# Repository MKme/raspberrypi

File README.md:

# raspi

<p align="center">
<b>Erics Raspberry Pi Randomness</b><br>
Open Source<br><br>
<br>🐦 <a href="https://twitter.com/mkmeorg">Twitter</a>
| 📺 <a href="https://www.youtube.com/mkmeorg">YouTube</a>
| 🌍 <a href="http://www.mkme.org">mkme.org</a><br>
<br>
Support this project and become a patron on <a href="https://www.patreon.com/EricWilliam">Patreon</a>.<br>
Chat: <a href="https://discord.gg/j9S4Fgv">Discord</a></b>!
</p>

# Raspberry Pi Stuffz
My Boards, programming and ref materials and all my random notes and files to make life easier

# Handy Linux Commands
sudo reboot

man : gives manual on any command

clear

cntrl-L Does the same as clear

whoami

pwd    - print working diectory

cd ~   - back to home dir

cd /

top     - Shows a list of processes running q- to quit

rm     - remove file/direct

ls -l   :show details

ls -a   : all files including hidden

ls -p  :puts a / after directories

ls -la   : both details and all files

ls -lap   : USE THIS 

df -h    : Show disk space!

sudo- gives root permissions

mv -move

mkdir

sudo -i Become Root

exit or ctrl-D to exit Root superuser

help popd | more  -if a command doesnt have a manual try help 

ifconfig -Show network connections

ip address - IP info

ip maddress - MAC adress

whoami -Tells you username

$(whoami) runs command and uses the result for piping

ps aux | grep -v $(whoami) - Returns all process running Not by current user (-v means NOT equal in Linux)

file test.py -File gives the info on what a file is and whats inside- 

less test.py -Command line text editor- Q to quit

acl -calendar

cat > test.txt  -Will pipe your typed output to file, Ctrl-D to exit

Bash- learn more on this- should be on all systems

Running Scripts:

sh test.py will run test in shell

Type chmod a+x hello.py to make executable

Type ./hello.py to run your program!

GetLinux Releaxse Info:

more /etc/*release   

or

cat /etc/*release

free -h  -Free memory stats in human readable with -h

df -h -Gives free disk space

locate xxx  -Will search the file index and return results found

find /etc/ -name *.conf    -Will return all conf files in that directory & subdirectories

Cool Screensaver in terminal!

cmatrix -s -Once installed via apt-get install -s will exit from any key.  AWESOME screensaver -bs for bold

### Handy  

Awesome tutorial dual boot etc and Kodi
https://www.youtube.com/watch?v=hLs5V-GNJjg

Scratch with Kinect-Awesome
https://www.youtube.com/watch?v=LpPDnRVIYcM

Screencapture/VNC connection to Pi!
https://www.youtube.com/watch?v=EfAmq8TgHes

Basic setup to achieve above VNC:
https://www.youtube.com/watch?v=c5QCoh8S0N4

VNC into Pi- Some great tips on finding it!  End is complex with ssh etc
https://www.youtube.com/watch?v=S6tnNBlqtNI

##VNC 

Install vnc:

sudo apt-get install tightvncserver

tightvncserver

Add password:raspberr

vncserver :1 -geometry 800x600 -depth 24

or

vncserver :1 -geometry 1280x720 -depth 24

##HANDY 

E- WORKS but need to login via ssh Start VNC on Startup:  https://www.youtube.com/watch?v=JXnnhTvvVZk

ADA version no worky  https://learn.adafruit.com/adafruit-raspberry-pi-lesson-7-remote-control-with-vnc/running-vncserver-at-startup

*****E note- do ADA method via vnc file access then it works but you MUST enable boot to desktop in raspi-config

*******E Note- Copy Paste does not work by default- follow this to fix then all good!  http://raspberrypi.stackexchange.com/questions/4474/tightvnc-copy-paste-between-local-os-and-raspberry-pi

FTP Just use filezilla to port 22!!!!

Install FTP:

sudo apt-get install ftpd

Total Commander works perfect after this just use user and password 

Port 22

https://www.youtube.com/watch?v=Ua1BEDfck-E

Install Python Environment:
sudo apt-get install spe
Video:  https://www.youtube.com/watch?v=UUOCh0Cbty8

GNURadio: Still need to demodulate the below 2
https://avidbit.com/putting-the-rpi-2-through-its-paces-with-gnuradio/
http://www.rs-online.com/designspark/electronics/eng/blog/taking-the-raspberry-pi-2-for-a-test-drive-with-gnu-radio-2?/designspark/electronics/blog/taking-the-raspberry-pi-2-for-a-test-drive-with-gnu-radio-2=

Thermal Printer:
https://learn.adafruit.com/pi-thermal-printer/pi-setup-part-2
installed git repo and python something else...

Another better tutorial?:

https://www.youtube.com/watch?v=TC9V7cotUgw

Polaroidthermalprinter
https://www.youtube.com/watch?v=mB7xRSPQbF4

Arduino:
http://spellfoundry.com/sleepy-pi/setting-arduino-ide-raspbian/

OpenCV for Cam stuff:
Install: http://www.pyimagesearch.com/2015/07/27/installing-opencv-3-0-for-both-python-2-7-and-python-3-on-your-raspberry-pi-2/

Chromium:
sudo apt-get chromium   - Thats it

Scrrensot command?

Libre tutorial- make a video on this:
https://www.youtube.com/watch?v=CxK4IZ0_Aao

Personalization- 

Show how to put start at bottom

Add progs to task bar

In Terminal Change font size under preferences

Tethering Internet:

https://www.raspberrypi.org/forums/viewtopic.php?f=29&t=90728

https://www.youtube.com/watch?v=x_yhJ_QBfaU

Text 2 speech engine - install festival

### Attribution

This work is licensed under a Creative Commons Attribution-NonCommercial 4.0 International License.
https://creativecommons.org/licenses/by-nc/4.0/

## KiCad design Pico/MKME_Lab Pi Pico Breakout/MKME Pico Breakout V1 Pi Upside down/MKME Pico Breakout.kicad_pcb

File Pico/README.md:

<p align="center">
<b>Erics Raspberry Pi PICO<br>
<br><br>
<br>🐦 <a href="https://twitter.com/mkmeorg">Twitter</a>
| 📺 <a href="https://www.youtube.com/mkmeorg">YouTube</a>
| 🌍 <a href="http://www.mkme.org">mkme.org</a><br>
<br>
Support this project and become a patron on <a href="https://www.patreon.com/EricWilliam">Patreon</a>.<br>
Chat: <a href="https://discord.gg/j9S4Fgv">Discord</a></b>!
</p>

# Raspberry Pi Pico Parts

Buy a breakout board here: https://store.mkme.org/?product=raspberry-pi-pico-breakout-pcb-with-screw-terminals-v1

# Handy Stuff 

My Boards, programming and ref materials and all my random notes and files to make life easier

- SSD1306 I2C OLED https://www.youtube.com/watch?v=vVS4gFI5gjM&ab_channel=anErik  Also includes handy info on how to use Thonny to create a lib file on the Pico

- SSD1306 again https://www.youtube.com/watch?v=Csmu8svTN4s&ab_channel=GaryExplains

#  128X32 SSD1306 OLED

https://github.com/raspberrypi/micropython/blob/pico/drivers/display/ssd1306.py  
 
-  Save this as ssd1306.py   to the pico
-  Use this as main.py inverting text (located in folder here)

Handy site: https://www.mfitzp.com/article/oled-displays-i2c-micropython/

Pico invaders code https://github.com/printnplay/Pico-MicroPython/blob/main/picoinvaders.py

Pico invaders ssd1306   https://www.youtube.com/watch?v=O5S1LC5TFiM&ab_channel=Print%27NPlay

# Other Handy Stuff

- Handy info on REPL and sending soft reboot to check main.py https://github.com/thonny/thonny/wiki/MicroPython#managing-other-files

- Install Circuitpython https://www.youtube.com/watch?v=WqjT4cdATxo&ab_channel=anErik

-  C Coding https://www.youtube.com/watch?v=il4bgA76E1M&ab_channel=BenHeckHacks

- IO https://www.youtube.com/watch?v=Zy64kZEM_bg&ab_channel=DroneBotWorkshop

### Pinout

### kicad footprint

https://github.com/HeadBoffin/RP_Silicon_KiCad

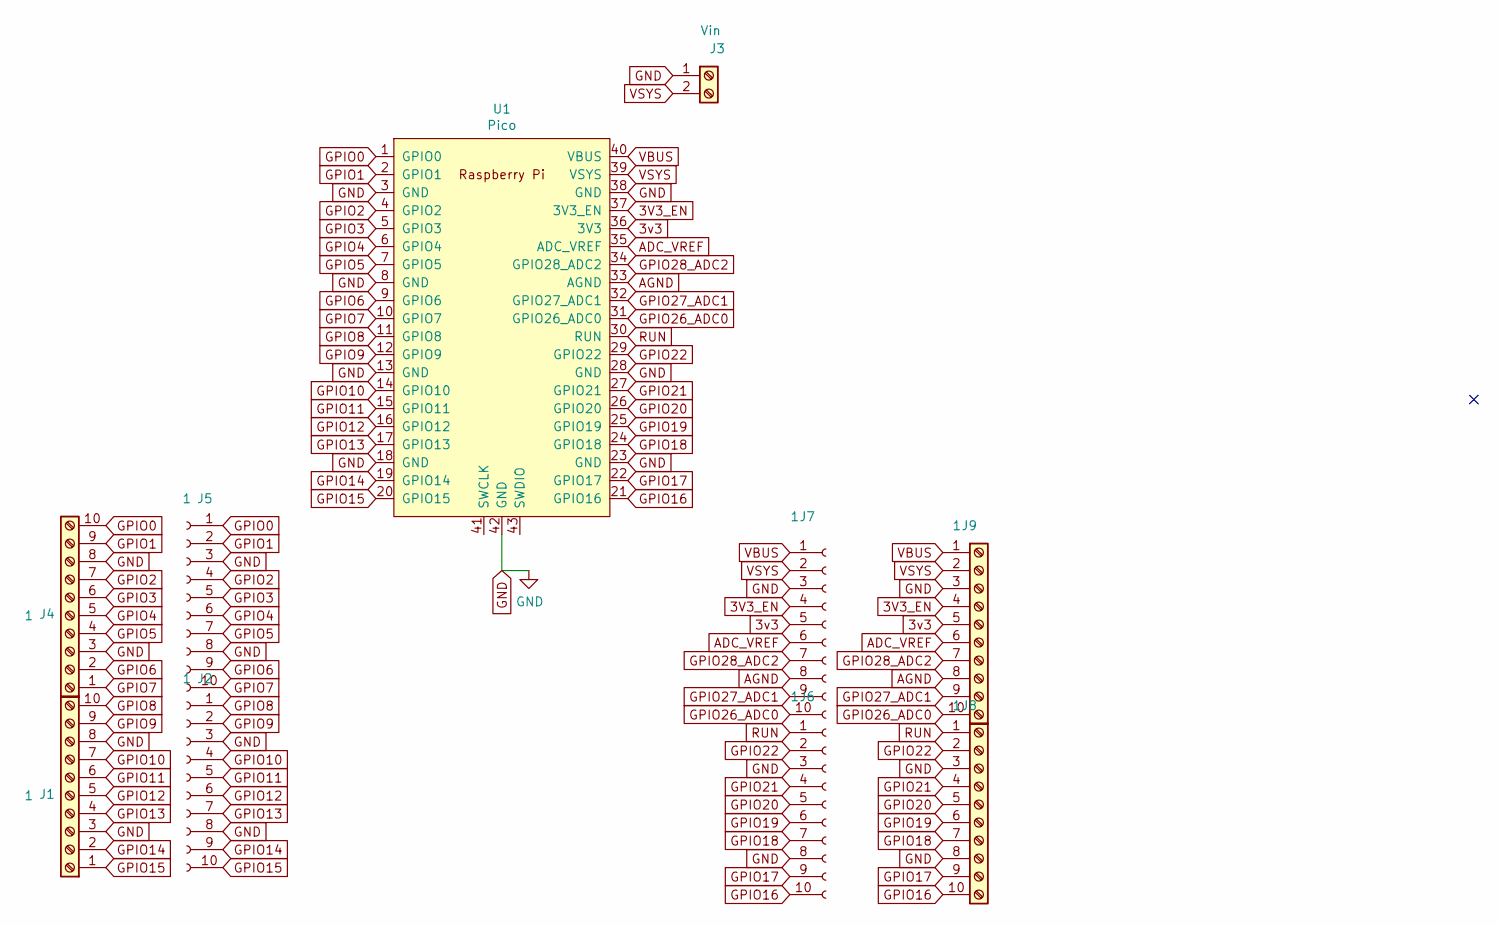
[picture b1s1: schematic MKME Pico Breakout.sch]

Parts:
J1, J4, J8, J9: 1; TerminalBlock_RND_205-00295_1x10_P5.08mm_Horizontal
J2, J5, J6, J7: 1; PinHeader_1x10_P2.54mm_Vertical
J3: Vin; TerminalBlock_RND_205-00287_1x02_P5.08mm_Horizontal
U1: Pico; RPi_Pico_SMD_TH

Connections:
3V3_EN: J7.4, J9.4, U1.37 (3V3_EN)
3v3: J7.5, J9.5, U1.36 (3V3)
ADC_VREF: J7.6, J9.6, U1.35 (ADC_VREF)
AGND: J7.8, J9.8, U1.33 (AGND)
GND: J1.3, J1.8, J2.3, J2.8, J3.1, J4.3, J4.8, J5.3, J5.8, J6.3, J6.8, J7.3, J8.3, J8.8, J9.3, U1.3 (GND), U1.8 (GND), U1.13 (GND), U1.18 (GND), U1.23 (GND), U1.28 (GND), U1.38 (GND), U1.42 (GND)
GPIO0: J4.10, J5.1, U1.1 (GPIO0)
GPIO1: J4.9, J5.2, U1.2 (GPIO1)
GPIO2: J4.7, J5.4, U1.4 (GPIO2)
GPIO3: J4.6, J5.5, U1.5 (GPIO3)
GPIO4: J4.5, J5.6, U1.6 (GPIO4)
GPIO5: J4.4, J5.7, U1.7 (GPIO5)
GPIO6: J4.2, J5.9, U1.9 (GPIO6)
GPIO7: J4.1, J5.10, U1.10 (GPIO7)
GPIO8: J1.10, J2.1, U1.11 (GPIO8)
GPIO9: J1.9, J2.2, U1.12 (GPIO9)
GPIO10: J1.7, J2.4, U1.14 (GPIO10)
GPIO11: J1.6, J2.5, U1.15 (GPIO11)
GPIO12: J1.5, J2.6, U1.16 (GPIO12)
GPIO13: J1.4, J2.7, U1.17 (GPIO13)
GPIO14: J1.2, J2.9, U1.19 (GPIO14)
GPIO15: J1.1, J2.10, U1.20 (GPIO15)
GPIO16: J6.10, J8.10, U1.21 (GPIO16)
GPIO17: J6.9, J8.9, U1.22 (GPIO17)
GPIO18: J6.7, J8.7, U1.24 (GPIO18)
GPIO19: J6.6, J8.6, U1.25 (GPIO19)
GPIO20: J6.5, J8.5, U1.26 (GPIO20)
GPIO21: J6.4, J8.4, U1.27 (GPIO21)
GPIO22: J6.2, J8.2, U1.29 (GPIO22)
GPIO26_ADC0: J7.10, J9.10, U1.31 (GPIO26_ADC0)
GPIO27_ADC1: J7.9, J9.9, U1.32 (GPIO27_ADC1)
GPIO28_ADC2: J7.7, J9.7, U1.34 (GPIO28_ADC2)
RUN: J6.1, J8.1, U1.30 (RUN)
VBUS: J7.1, J9.1, U1.40 (VBUS)
VSYS: J3.2, J7.2, J9.2, U1.39 (VSYS)

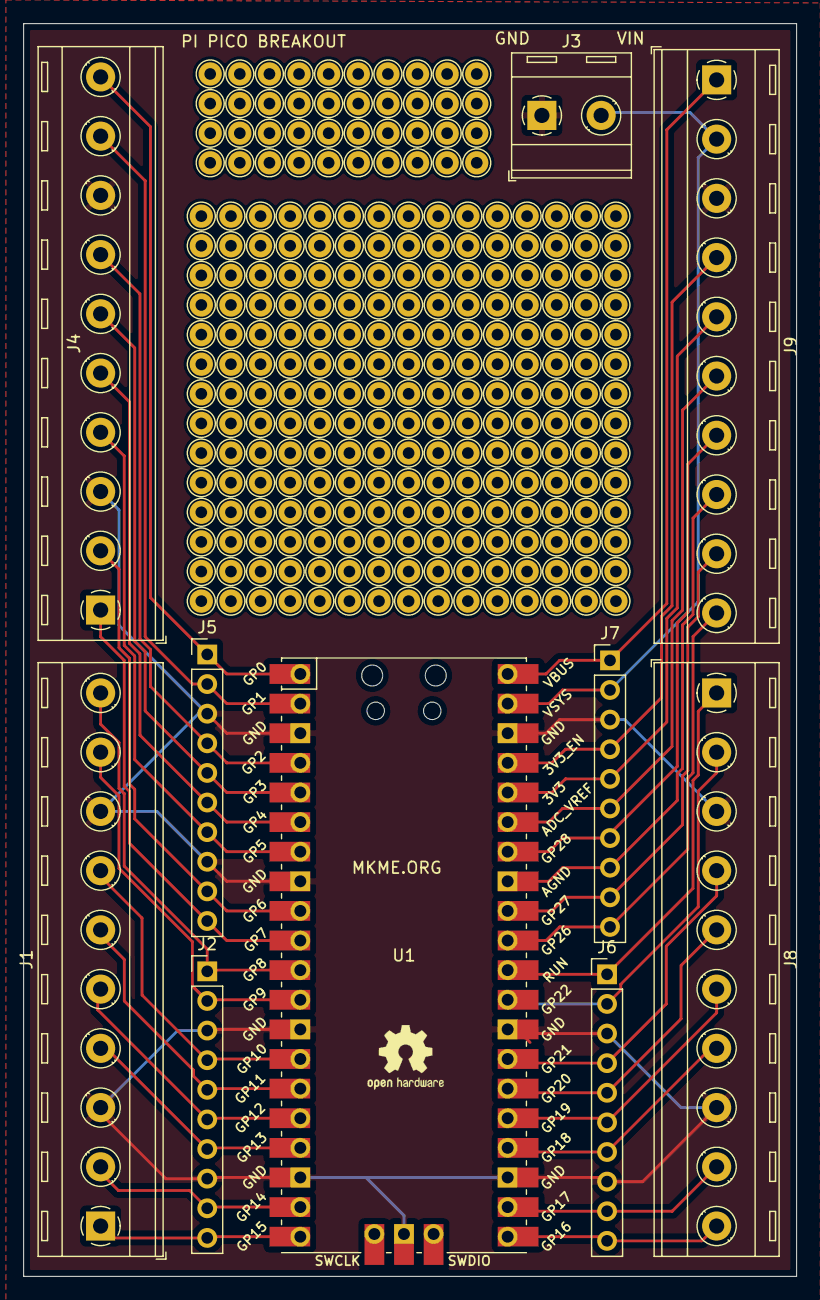
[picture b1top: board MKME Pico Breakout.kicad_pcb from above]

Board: 2 copper layers, 66.3 x 107.4 mm, 10 parts (0 on the bottom side), 34 nets.

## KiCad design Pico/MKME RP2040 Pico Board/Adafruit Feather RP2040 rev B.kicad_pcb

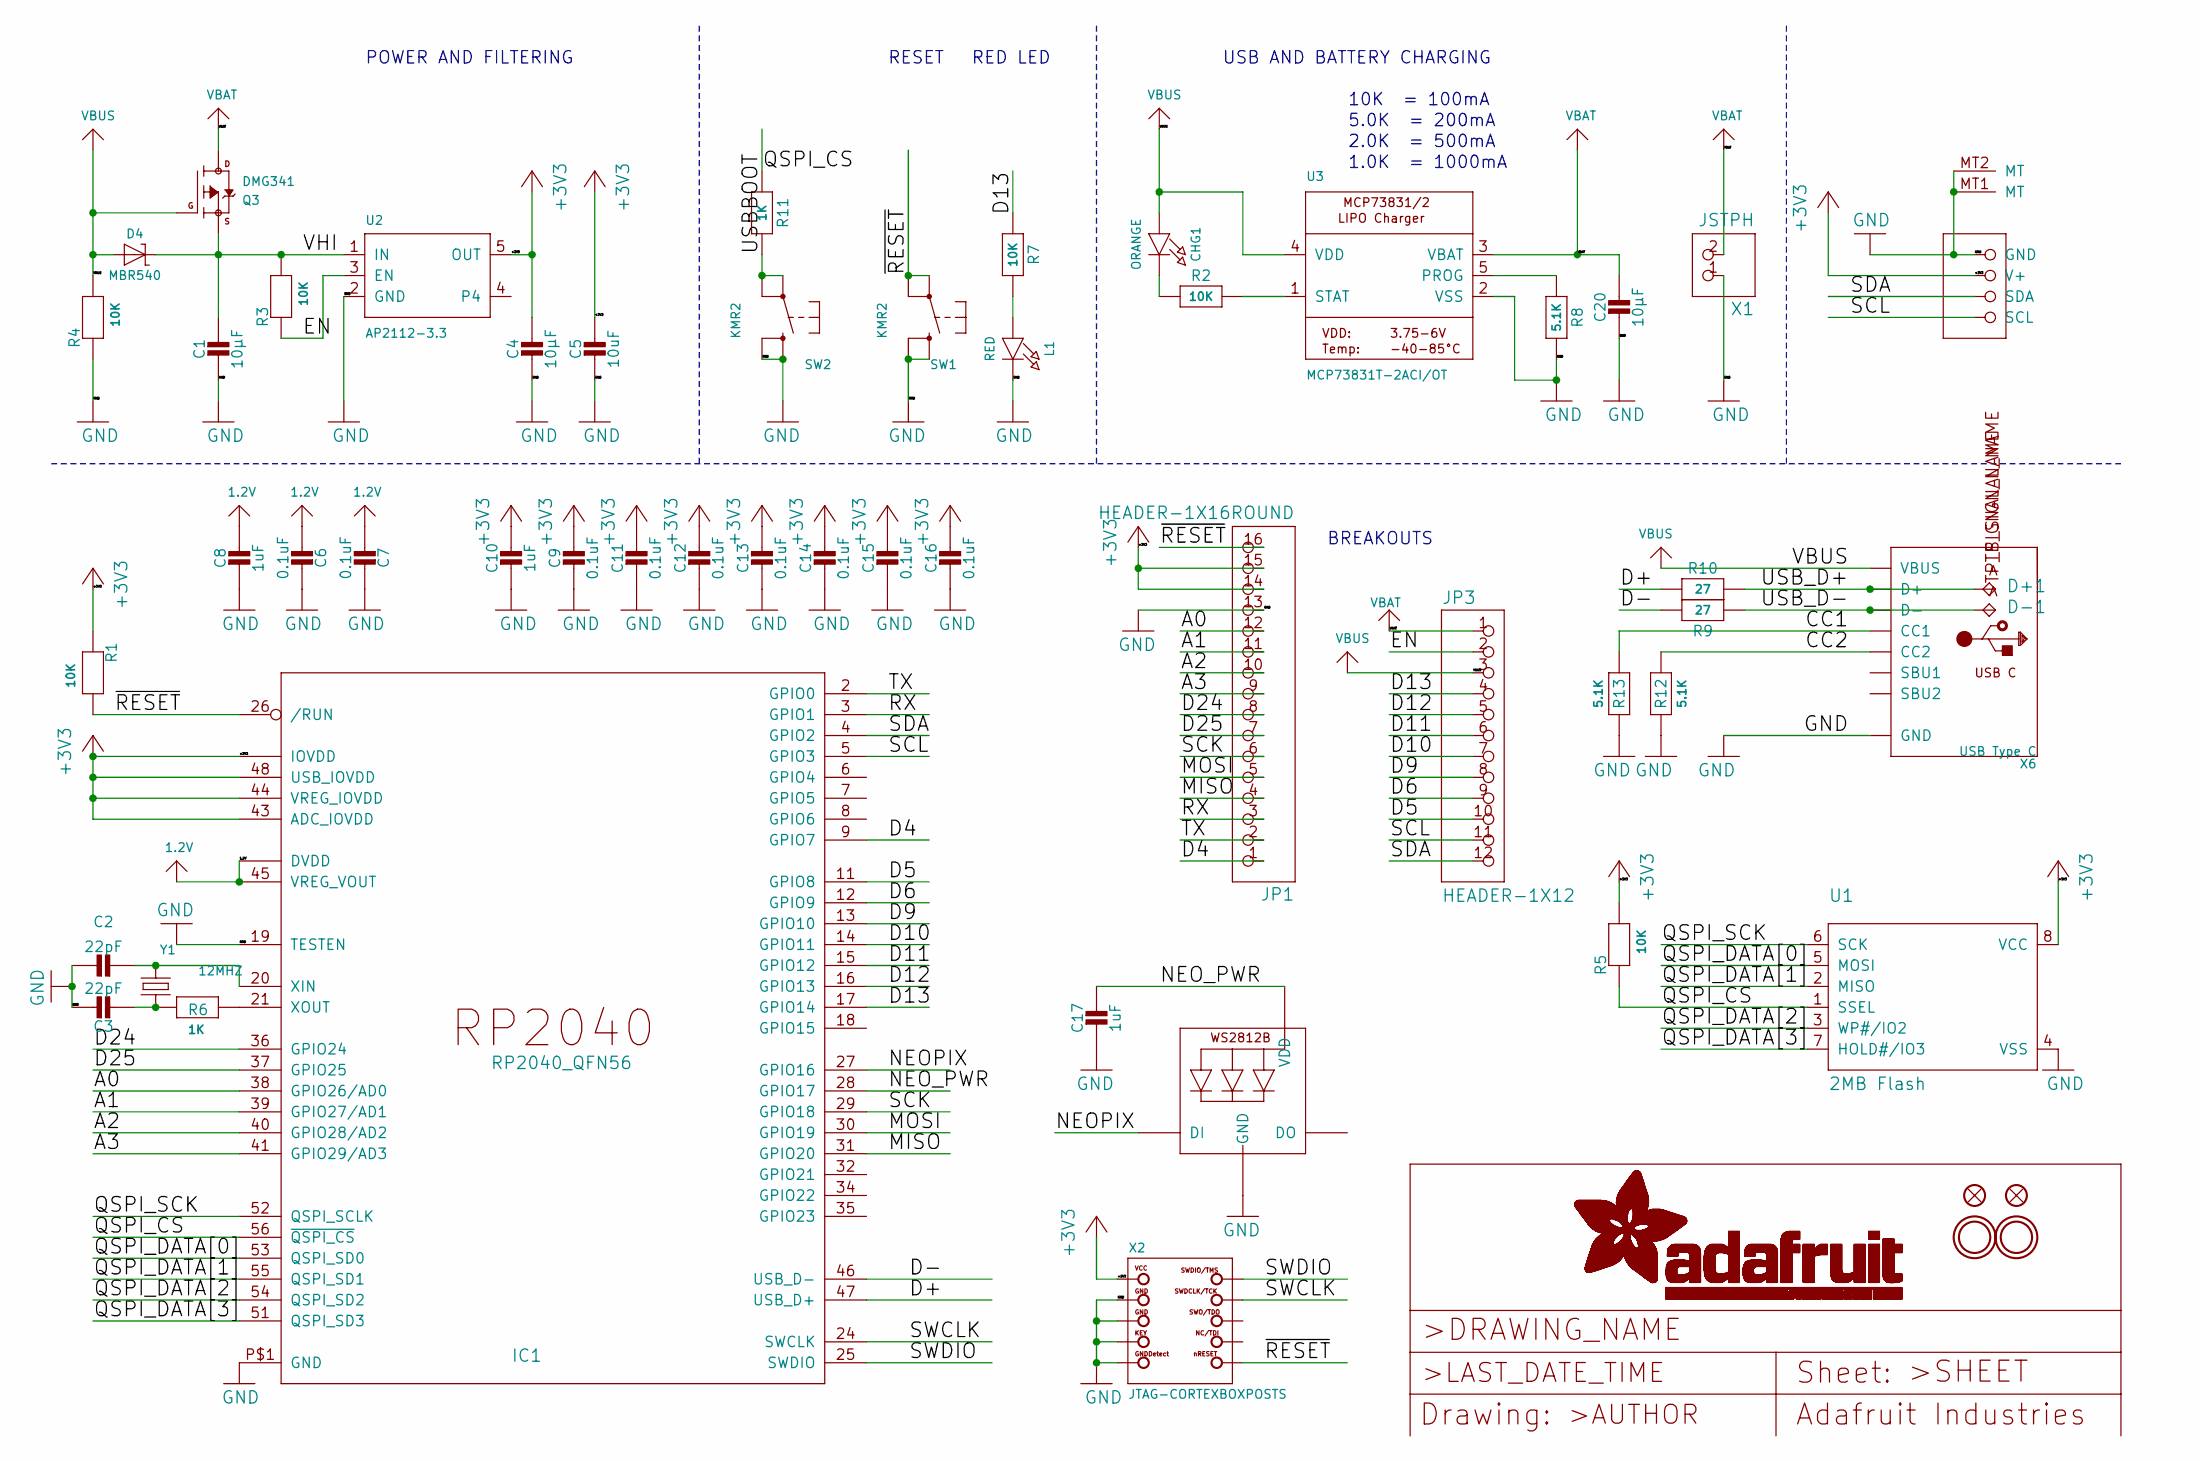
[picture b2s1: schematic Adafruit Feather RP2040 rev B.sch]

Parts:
C1, C4, C20: 10µF; 0805-NO
C2, C3: 22pF; 0603-NO
C5: 10uF; 0805-NO
C6, C7, C9, C11, C12, C13, C14, C15, C16: 0.1uF; 0603-NO
C8, C10, C17: 1uF; 0603-NO
CHG1: ORANGE; CHIPLED_0603_NOOUTLINE
CONN1: STEMMA_I2C_QT; JST_SH4
D4: MBR540; SOD-123
D+1: TPB1,27; B1,27
D-1: TPB1,27; B1,27
IC1: RP2040_QFN56; QFN56_7MM_REDUCEDEPAD
JP1: HEADER-1X16ROUND; 1X16_ROUND
JP3: HEADER-1X12; 1X12_ROUND
L1: RED; CHIPLED_0603_NOOUTLINE
LED1: WS2812B3535; LED3535
Q3: DMG341; SOT23-R
R1, R2, R3, R4, R5, R7: 10K; 0603-NO
R6, R11: 1K; 0603-NO
R8, R12, R13: 5.1K; 0603-NO
R9, R10: 27; 0603-NO
SW1, SW2: KMR2; BTN_KMR2_4.6X2.8
U1: 2MB Flash; SOIC8_208MIL
U2: AP2112-3.3; SOT23-5@1
U3: MCP73831T-2ACI/OT; SOT23-5
U$31, U$32: MOUNTINGHOLE2.5; MOUNTINGHOLE_2.5_PLATED
U$34, U$35: FIDUCIAL_1MM
X1: JSTPH; JSTPH2_BATT
X2: JTAG-CORTEXBOXPOSTS; 2X05_1.27MM_BOX_POSTS
X6: USB Type C; USB_C_CUSB31-CFM2AX-01-X
Y1: 12MHZ; CRYSTAL_2.5X2

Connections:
1.2V: C6.2, C7.2, C8.1, IC1.23 (DVDD), IC1.45 (VREG_VOUT), IC1.50 (DVDD)
+3V3: C4.1, C5.1, C9.1, C10.1, C11.1, C12.1, C13.1, C14.1, C15.1, C16.1, CONN1.2 (V+), IC1.1 (IOVDD), IC1.10 (IOVDD), IC1.22 (IOVDD), IC1.33 (IOVDD), IC1.42 (IOVDD), IC1.43 (ADC_IOVDD), IC1.44 (VREG_IOVDD), IC1.48 (USB_IOVDD), IC1.49 (IOVDD), JP1.14, JP1.15, R1.1, R5.2, U1.8 (VCC), U2.5 (OUT), X2.1 (VCC)
/A0: IC1.38 (GPIO26/AD0), JP1.12
/A1: IC1.39 (GPIO27/AD1), JP1.11
/A2: IC1.40 (GPIO28/AD2), JP1.10
/A3: IC1.41 (GPIO29/AD3), JP1.9
/CC1: R13.2, X6.A5 (CC1)
/CC2: R12.2, X6.B5 (CC2)
/D4: IC1.9 (GPIO7), JP1.1
/D5: IC1.11 (GPIO8), JP3.10
/D6: IC1.12 (GPIO9), JP3.9
/D9: IC1.13 (GPIO10), JP3.8
/D10: IC1.14 (GPIO11), JP3.7
/D11: IC1.15 (GPIO12), JP3.6
/D12: IC1.16 (GPIO13), JP3.5
/D13: IC1.17 (GPIO14), JP3.4, R7.1
/D24: IC1.36 (GPIO24), JP1.8
/D25: IC1.37 (GPIO25), JP1.7
/D+: IC1.47 (USB_D+), R10.2
/D-: IC1.46 (USB_D-), R9.2
/EN: JP3.2, R3.1, U2.3 (EN)
/MISO: IC1.31 (GPIO20), JP1.4
/MOSI: IC1.30 (GPIO19), JP1.5
/NEOPIX: IC1.27 (GPIO16), LED1.1 (DI)
/NEO_PWR: C17.1, IC1.28 (GPIO17), LED1.2 (VDD)
/QSPI_CS: IC1.56 (~QSPI_CS), R5.1, R11.1, U1.1 (SSEL)
/QSPI_DATA[0]: IC1.53 (QSPI_SD0), U1.5 (MOSI)
/QSPI_DATA[1]: IC1.55 (QSPI_SD1), U1.2 (MISO)
/QSPI_DATA[2]: IC1.54 (QSPI_SD2), U1.3 (WP#/IO2)
/QSPI_DATA[3]: IC1.51 (QSPI_SD3), U1.7 (HOLD#/IO3)
/QSPI_SCK: IC1.52 (QSPI_SCLK), U1.6 (SCK)
/RX: IC1.3 (GPIO1), JP1.3
/SCK: IC1.29 (GPIO18), JP1.6
/SCL: CONN1.4 (SCL), IC1.5 (GPIO3), JP3.11
/SDA: CONN1.3 (SDA), IC1.4 (GPIO2), JP3.12
/SWCLK: IC1.24 (SWCLK), X2.4 (SWDCLK)
/SWDIO: IC1.25 (SWDIO), X2.2 (SWDIO)
/TX: IC1.2 (GPIO0), JP1.2
/USBBOOT: R11.2, SW2.A, SW2.A' (P1)
/USB_D+: D+1.TP, R10.1, X6.A6 (D+), X6.B6 (D+)
/USB_D-: D-1.TP, R9.1, X6.A7 (D-), X6.B7 (D-)
/VHI: C1.1, D4.C, Q3.2 (S), R3.2, U2.1 (IN)
/~RESET: IC1.26 (/RUN), JP1.16, R1.2, SW1.A, SW1.A' (P1), X2.10 (NRESET)
GND: C1.2, C2.1, C3.1, C4.2, C5.2, C6.1, C7.1, C8.2, C9.2, C10.2, C11.2, C12.2, C13.2, C14.2, C15.2, C16.2, C17.2, C20.2, CONN1.1 (GND), CONN1.MT1 (MT), CONN1.MT2 (MT), IC1.19 (TESTEN), IC1.P$1 (GND), JP1.13, L1.C, LED1.4 (GND), R4.1, R8.2, R12.1, R13.1, SW1.B (S), SW1.B' (S1), SW2.B (S), SW2.B' (S1), U1.4 (VSS), U2.2 (GND), U3.2 (VSS), X1.1, X2.3 (GND@1), X2.5 (GND@2), X2.7 (KEY), X2.9 (GNDDETECT), X6.A1B12 (GND), X6.B1A12 (GND)
unnamed: C2.2, IC1.20 (XIN), Y1.3 (2)
unnamed: C3.2, R6.1, Y1.1
unnamed: CHG1.C, R2.1
unnamed: IC1.21 (XOUT), R6.2
unnamed: L1.A, R7.2
unnamed: R2.2, U3.1 (STAT)
unnamed: R8.1, U3.5 (PROG)
VBAT: C20.1, JP3.1, Q3.3 (D), U3.3 (VBAT), X1.2
VBUS: CHG1.A, D4.A, JP3.3, Q3.1 (G), R4.2, U3.4 (VDD), X6.A4B9 (VBUS), X6.B4A9 (VBUS)

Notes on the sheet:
POWER AND FILTERING
RESET
10K = 100mA
5.0K = 200mA
2.0K = 500mA
1.0K = 1000mA
USB AND BATTERY CHARGING
BREAKOUTS
RED LED

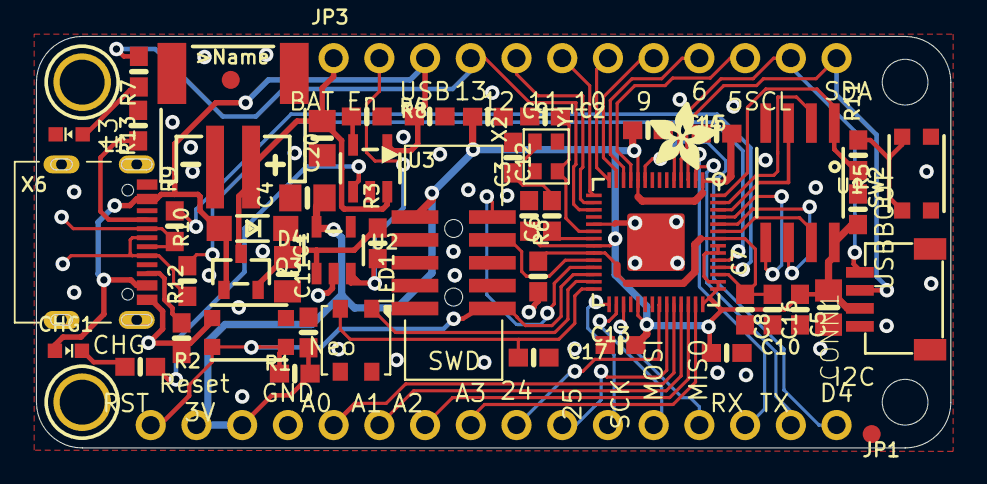
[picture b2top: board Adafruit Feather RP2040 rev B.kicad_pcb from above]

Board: 2 copper layers, 50.8 x 22.9 mm, 61 parts (0 on the bottom side), 53 nets.

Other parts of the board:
@HOLE0, @HOLE1: (no value)
U$9: FEATHERLOGO
U$12, U$28: ADAFRUIT_3.5MM
U$13: PCBFEAT-REV-040

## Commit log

2021-01-25 File Updates
2021-01-25 Tensor Flow added
2021-01-25 Machine Learning
2021-01-25 ML Updates
2021-01-25 Tensor Flow Changes
2021-01-25 Links
2021-01-25 Machine Learning Moved to own repo
2021-01-29 Adafruit RP2020 Adapted for my use R1
2021-01-30 Micropython files
2021-01-30 readme
2021-02-03 Pico Breakout Board
2021-02-09 Pi Pico boards added
    Not finished
2021-02-14 SSD1306 Demo
2021-02-14 Shield
2021-02-14 fixy
2021-02-14 Reworks
2021-02-15 debugging
2021-02-15 test
2021-02-16 Spacey
2021-02-16 fixed for oled no init on battery
2021-02-21 moar oled
2021-08-10 Final design
2021-10-07 Makerfabs Pico Primer Kit testing
